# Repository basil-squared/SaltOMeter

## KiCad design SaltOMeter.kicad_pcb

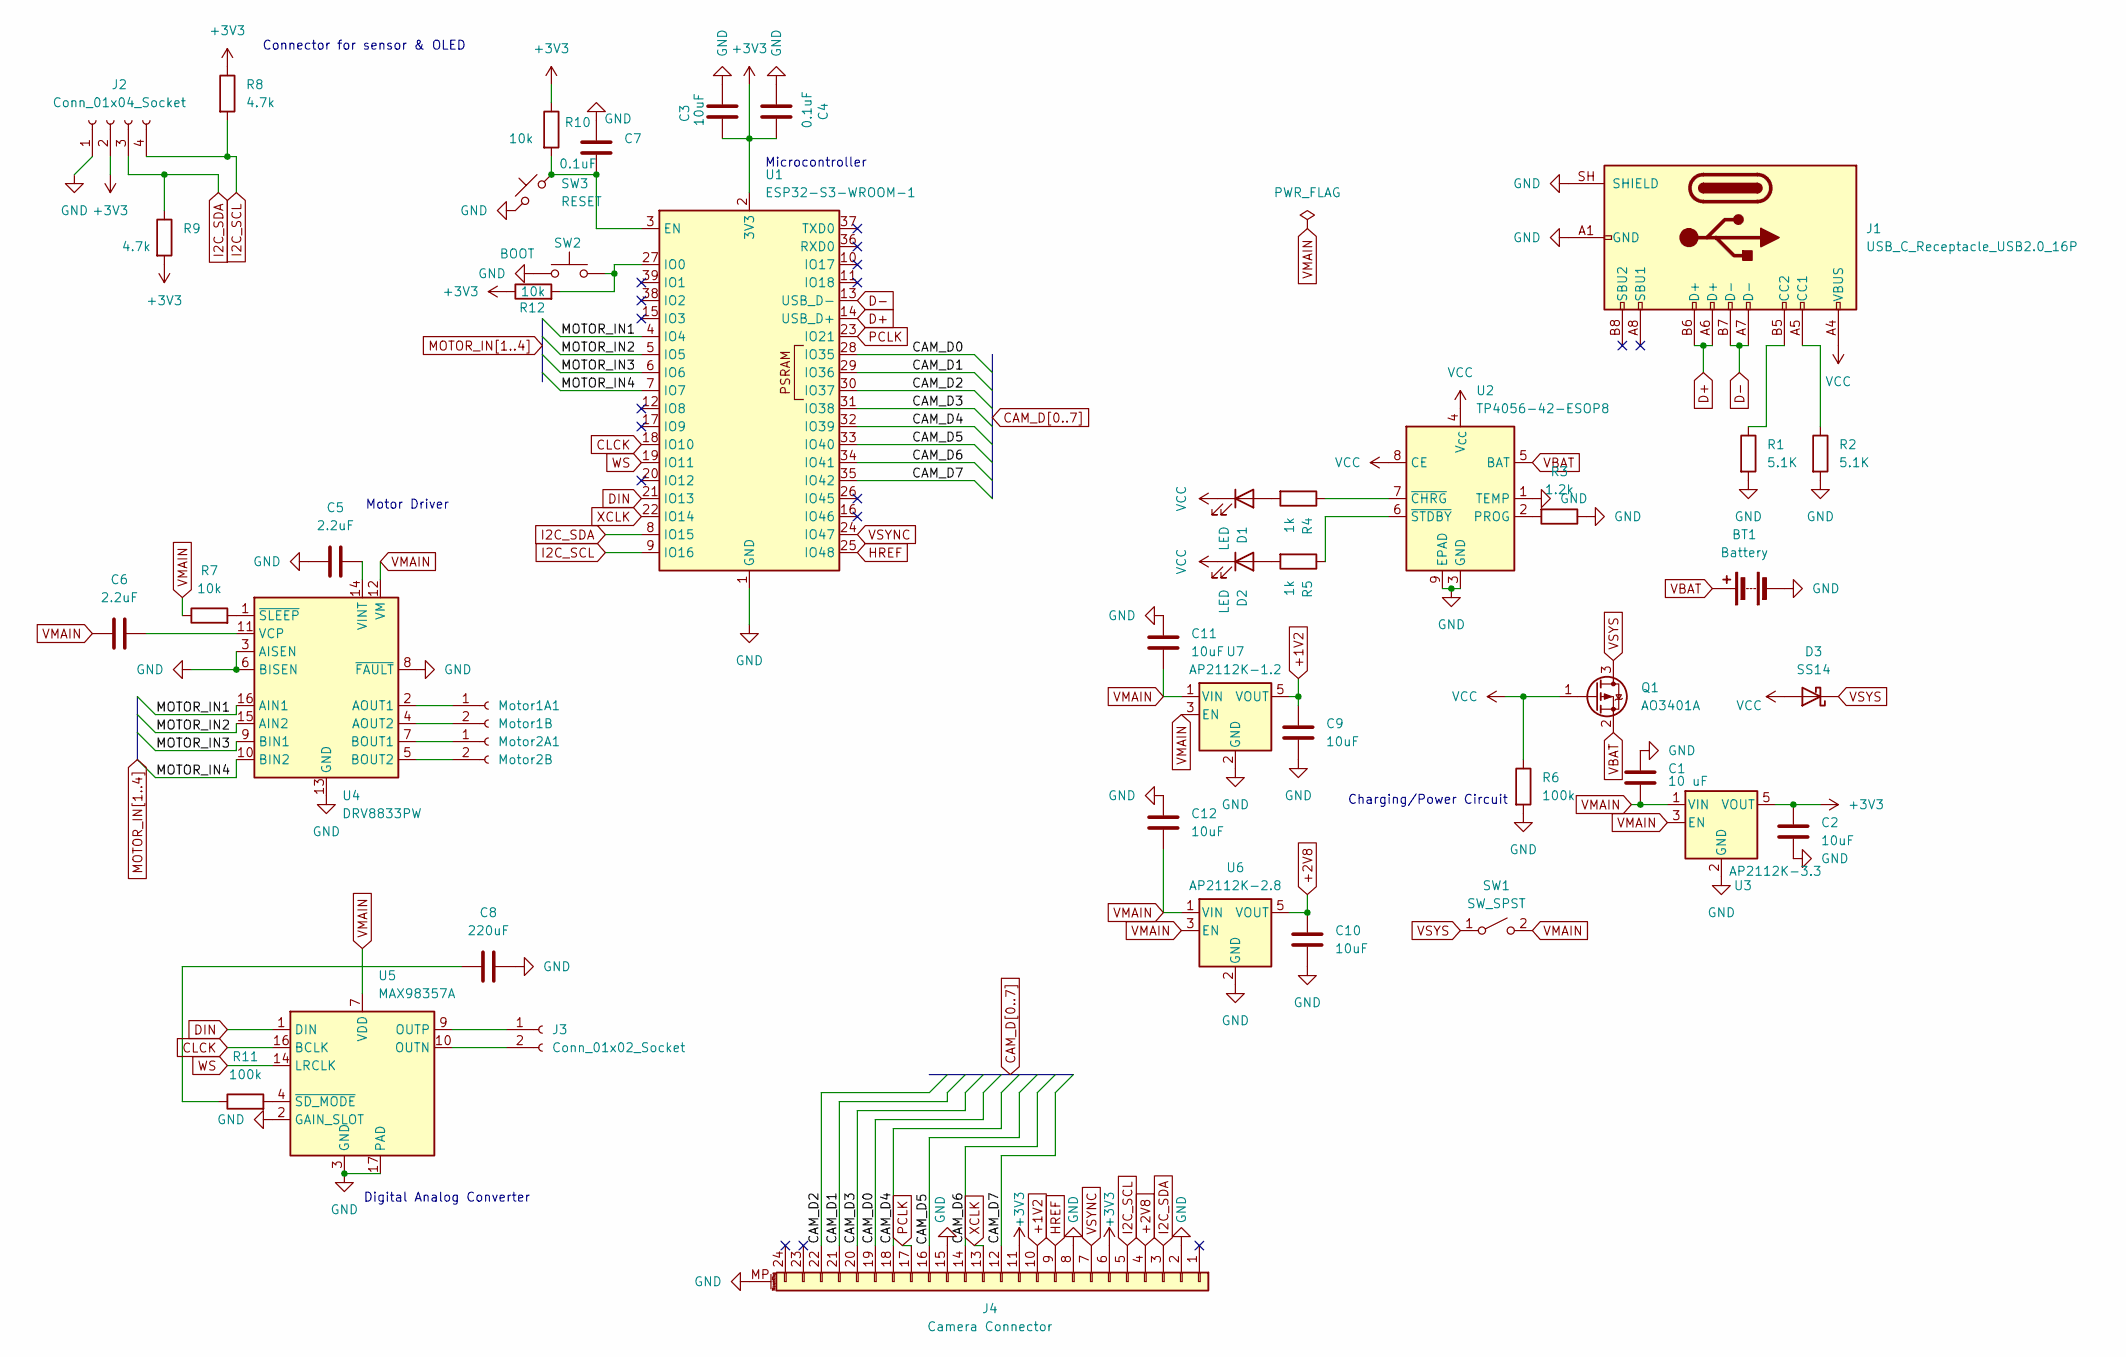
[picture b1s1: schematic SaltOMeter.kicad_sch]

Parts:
BT1: Battery; JST_PH_S2B-PH-K_1x02_P2.00mm_Horizontal
C1: 10 uF; C_0805_2012Metric_Pad1.18x1.45mm_HandSolder
C2, C3, C9, C10, C11, C12: 10uF; C_0805_2012Metric_Pad1.18x1.45mm_HandSolder
C4, C7: 0.1uF; C_0805_2012Metric_Pad1.18x1.45mm_HandSolder
C5, C6: 2.2uF; C_0805_2012Metric_Pad1.18x1.45mm_HandSolder
C8: 220uF; C_0805_2012Metric_Pad1.18x1.45mm_HandSolder
D1, D2: LED; LED_0805_2012Metric_Pad1.15x1.40mm_HandSolder
D3: SS14; D_SMA
J1: USB_C_Receptacle_USB2.0_16P; USB_C_Receptacle_HRO_TYPE-C-31-M-12
J2: Conn_01x04_Socket; JST_XH_B4B-XH-A_1x04_P2.50mm_Vertical
J3: Conn_01x02_Socket; JST_XH_B2B-XH-AM_1x02_P2.50mm_Vertical
J4: Camera Connector; Molex_200528-0240_1x24-1MP_P1.00mm_Horizontal
Motor1A1: Motor1B; JST_XH_B2B-XH-A_1x02_P2.50mm_Vertical
Motor2A1: Motor2B; JST_XH_B2B-XH-A_1x02_P2.50mm_Vertical
Q1: AO3401A; SOT-23
R1, R2: 5.1K; R_0805_2012Metric_Pad1.20x1.40mm_HandSolder
R3: 1.2k; R_0805_2012Metric_Pad1.20x1.40mm_HandSolder
R4, R5: 1k; R_0805_2012Metric_Pad1.20x1.40mm_HandSolder
R6, R11: 100k; R_0805_2012Metric_Pad1.20x1.40mm_HandSolder
R7, R10, R12: 10k; R_0805_2012Metric_Pad1.20x1.40mm_HandSolder
R8, R9: 4.7k; R_0805_2012Metric_Pad1.20x1.40mm_HandSolder
SW1: SW_SPST; SW_Slide_SPDT_Straight_CK_OS102011MS2Q
SW2: BOOT; SW_SPST_B3S-1000
SW3: RESET; SW_SPST_B3S-1000
U1: ESP32-S3-WROOM-1
U2: TP4056-42-ESOP8; SOIC-8-1EP_3.9x4.9mm_P1.27mm_EP2.41x3.3mm_ThermalVias
U3: AP2112K-3.3; SOT-23-5
U4: DRV8833PW; TSSOP-16_4.4x5mm_P0.65mm
U5: MAX98357A; TQFN-16-1EP_3x3mm_P0.5mm_EP1.23x1.23mm
U6: AP2112K-2.8; SOT-23-5
U7: AP2112K-1.2; SOT-23-5

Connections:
+1V2: C9.1, J4.10, U7.5 (VOUT)
+2V8: C10.1, J4.4, U6.5 (VOUT)
+3V3: C2.1, C3.2, C4.1, J2.2, J4.6, J4.11, R8.1, R9.2, R10.1, R12.1, U1.2 (3V3), U3.5 (VOUT)
CAM_D0: J4.19, U1.28 (IO35)
CAM_D1: J4.21, U1.29 (IO36)
CAM_D2: J4.22, U1.30 (IO37)
CAM_D3: J4.20, U1.31 (IO38)
CAM_D4: J4.18, U1.32 (IO39)
CAM_D5: J4.16, U1.33 (IO40)
CAM_D6: J4.14, U1.34 (IO41)
CAM_D7: J4.12, U1.35 (IO42)
CLCK: U1.18 (IO10), U5.16 (BCLK)
D+: J1.A6 (D+), J1.B6 (D+), U1.14 (USB_D+)
D-: J1.A7 (D-), J1.B7 (D-), U1.13 (USB_D-)
DIN: U1.21 (IO13), U5.1 (DIN)
GND: BT1.2 (-), C1.2, C2.2, C3.1, C4.2, C5.1, C7.2, C8.2, C9.2, C10.2, C11.2, C12.1, J1.A1 (GND), J1.A12 (GND), J1.B1 (GND), J1.B12 (GND), J1.SH (SHIELD), J2.1, J4.2, J4.8, J4.15, J4.MP (MountPin), R1.2, R2.2, R3.1, R6.2, SW2.1, SW3.1, U1.1 (GND), U1.40 (GND), U1.41 (GND), U2.1 (TEMP), U2.3 (GND), U2.9 (EPAD), U3.2 (GND), U4.3 (AISEN), U4.6 (BISEN), U4.8 (~FAULT), U4.13 (GND), U5.2 (GAIN_SLOT), U5.3 (GND), U5.11 (GND), U5.15 (GND), U5.17 (PAD), U6.2 (GND), U7.2 (GND)
HREF: J4.9, U1.25 (IO48)
I2C_SCL: J2.4, J4.5, R8.2, U1.9 (IO16)
I2C_SDA: J2.3, J4.3, R9.1, U1.8 (IO15)
MOTOR_IN1: U1.4 (IO4), U4.16 (AIN1)
MOTOR_IN2: U1.5 (IO5), U4.15 (AIN2)
MOTOR_IN3: U1.6 (IO6), U4.9 (BIN1)
MOTOR_IN4: U1.7 (IO7), U4.10 (BIN2)
unnamed: C8.1, R11.1
unnamed: D1.2 (A), R4.2
unnamed: D2.2 (A), R5.2
unnamed: J1.A5 (CC1), R2.1
unnamed: J1.B5 (CC2), R1.1
unnamed: J3.1, U5.9 (OUTP)
unnamed: J3.2, U5.10 (OUTN)
unnamed: Motor1A1.1, U4.2 (AOUT1)
unnamed: Motor1A1.2, U4.4 (AOUT2)
unnamed: Motor2A1.1, U4.7 (BOUT1)
unnamed: Motor2A1.2, U4.5 (BOUT2)
unnamed: C7.1, R10.2, SW3.2, U1.3 (EN)
unnamed: R12.2, SW2.2, U1.27 (IO0)
unnamed: R3.2, U2.2 (PROG)
unnamed: R4.1, U2.7 (~CHRG)
unnamed: R5.1, U2.6 (~STDBY)
unnamed: C6.2, U4.11 (VCP)
unnamed: C5.2, U4.14 (VINT)
unnamed: R7.2, U4.1 (~SLEEP)
unnamed: R11.2, U5.4 (~SD_MODE)
PCLK: J4.17, U1.23 (IO21)
VBAT: BT1.1 (+), Q1.2 (S), U2.5 (BAT)
VCC: D1.1 (K), D2.1 (K), D3.2 (A), J1.A4 (VBUS), J1.A9 (VBUS), J1.B4 (VBUS), J1.B9 (VBUS), Q1.1 (G), R6.1, U2.4 (V_{CC}), U2.8 (CE)
VMAIN: C1.1, C6.1, C11.1, C12.2, R7.1, SW1.2 (B), U3.1 (VIN), U3.3 (EN), U4.12 (VM), U5.7 (VDD), U5.8 (VDD), U6.1 (VIN), U6.3 (EN), U7.1 (VIN), U7.3 (EN)
VSYNC: J4.7, U1.24 (IO47)
VSYS: D3.1 (K), Q1.3 (D), SW1.1 (A)
WS: U1.19 (IO11), U5.14 (LRCLK)
XCLK: J4.13, U1.22 (IO14)

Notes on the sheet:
Digital Analog Converter
Charging/Power Circuit
Motor Driver
Microcontroller
Connector for sensor & OLED

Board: 2 copper layers, 45 parts (0 on the bottom side), 51 nets, no tracks yet.

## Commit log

2026-04-26 init
2026-04-28 rgwgrfs
2026-04-28 add speaker and afefw
2026-05-01 Finish schematic and start work on PCB
2026-05-01 add fan
